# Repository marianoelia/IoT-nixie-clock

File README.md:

# Nixie Clock Project
[Link to hackster writeup tutorial](https://www.hackster.io/mrelia100/particle-photon-nixie-clock)

## Introduction
This is repo for my nixie clock build.

## License

This work is licensed under the  Creative Commons Attribution-ShareAlike 4.0 International License. To view a copy of this license, visit <http://creativecommons.org/licenses/by-sa/4.0/> or send a letter to Creative Commons, 444 Castro Street, Suite 900, Mountain View, California, 94041, USA.

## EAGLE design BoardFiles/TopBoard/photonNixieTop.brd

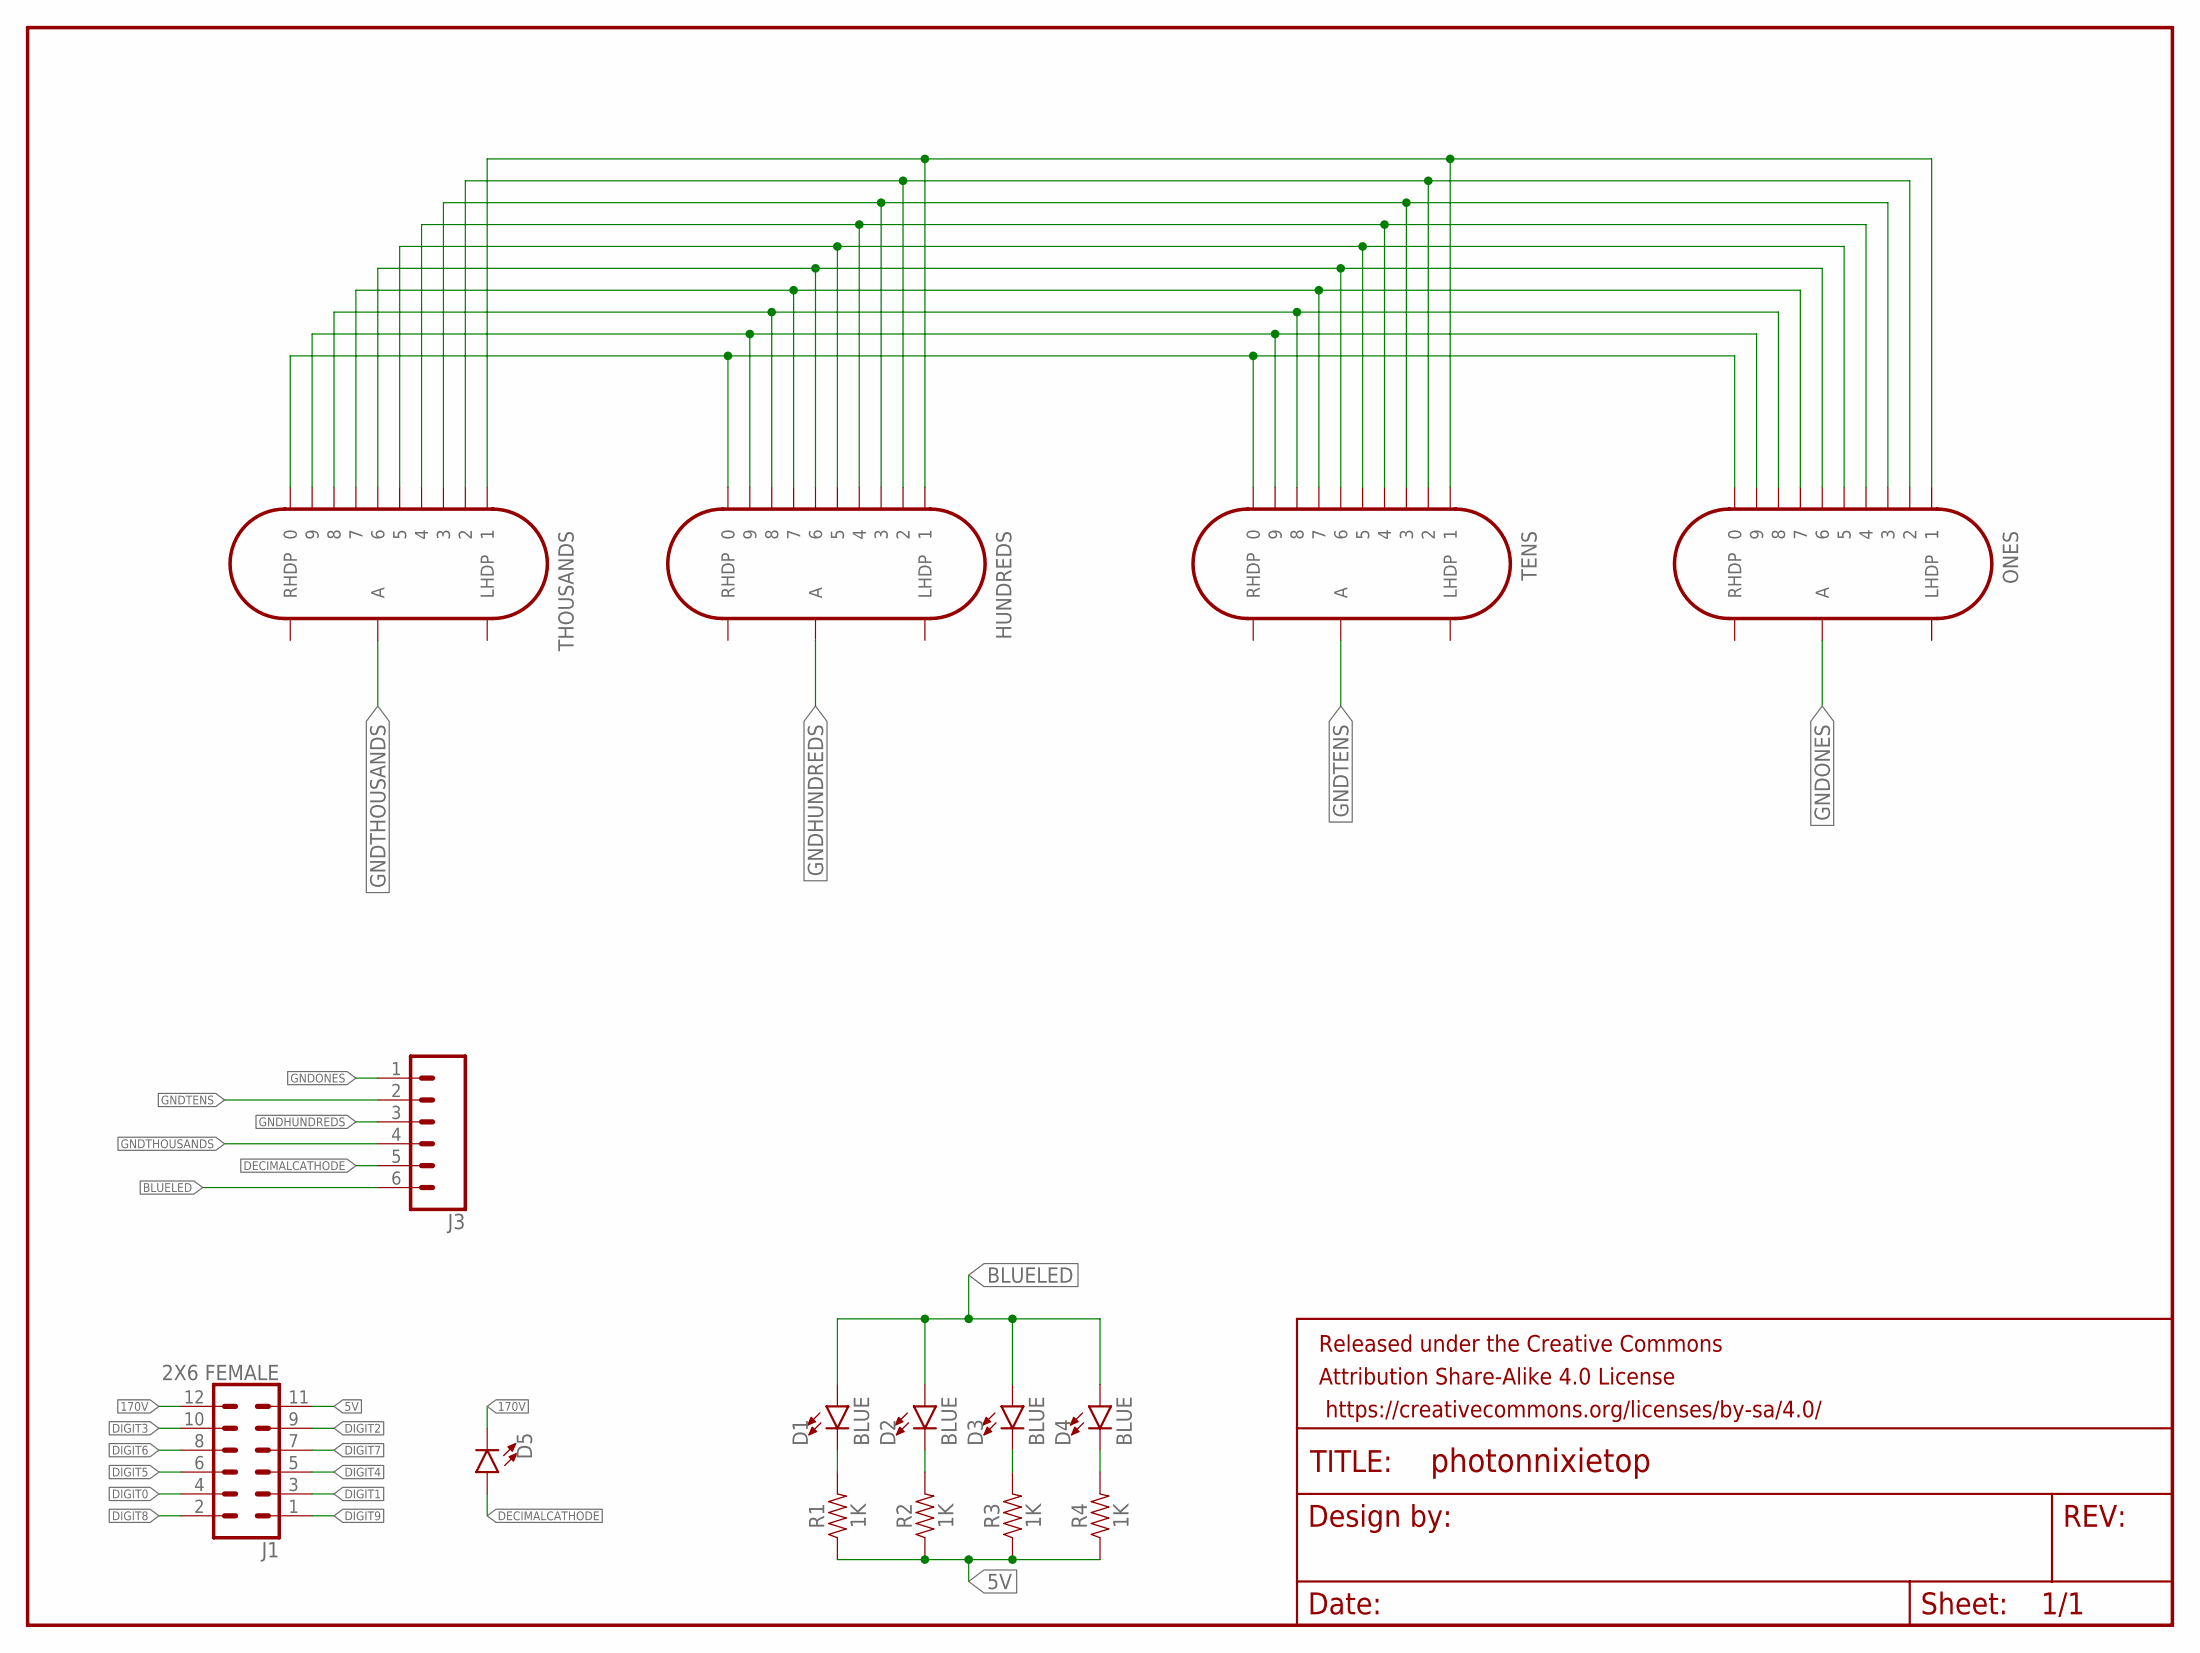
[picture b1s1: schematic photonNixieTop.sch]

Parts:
D1, D2, D3, D4: BLUE; LED-1206
D5: LED5MM; LED_5MM
FRAME1: FRAME-LETTER; CREATIVE_COMMONS
HUNDREDS: IN-14
J1: 2X6 FEMALE; 2X6
J3: CONN_06SILK_FEMALE_PTH; 1X06
ONES: IN-14
R1, R2, R3, R4: 1K; 0805
TENS: IN-14
THOUSANDS: IN-14

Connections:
5V: J1.11, R1.1, R2.1, R3.1, R4.1
170V: D5.K (C), J1.12
BLUELED: D1.A, D2.A, D3.A, D4.A, J3.6
DECIMALCATHODE: D5.A, J3.5
DIGIT0: HUNDREDS.0, J1.4, ONES.0, TENS.0, THOUSANDS.0
DIGIT1: HUNDREDS.1, J1.3, ONES.1, TENS.1, THOUSANDS.1
DIGIT2: HUNDREDS.2, J1.9, ONES.2, TENS.2, THOUSANDS.2
DIGIT3: HUNDREDS.3, J1.10, ONES.3, TENS.3, THOUSANDS.3
DIGIT4: HUNDREDS.4, J1.5, ONES.4, TENS.4, THOUSANDS.4
DIGIT5: HUNDREDS.5, J1.6, ONES.5, TENS.5, THOUSANDS.5
DIGIT6: HUNDREDS.6, J1.8, ONES.6, TENS.6, THOUSANDS.6
DIGIT7: HUNDREDS.7, J1.7, ONES.7, TENS.7, THOUSANDS.7
DIGIT8: HUNDREDS.8, J1.2, ONES.8, TENS.8, THOUSANDS.8
DIGIT9: HUNDREDS.9, J1.1, ONES.9, TENS.9, THOUSANDS.9
GNDHUNDREDS: HUNDREDS.A, J3.3
GNDONES: J3.1, ONES.A
GNDTENS: J3.2, TENS.A
GNDTHOUSANDS: J3.4, THOUSANDS.A
unnamed: D4.C, R4.2
unnamed: D3.C, R3.2
unnamed: D2.C, R2.2
unnamed: D1.C, R1.2

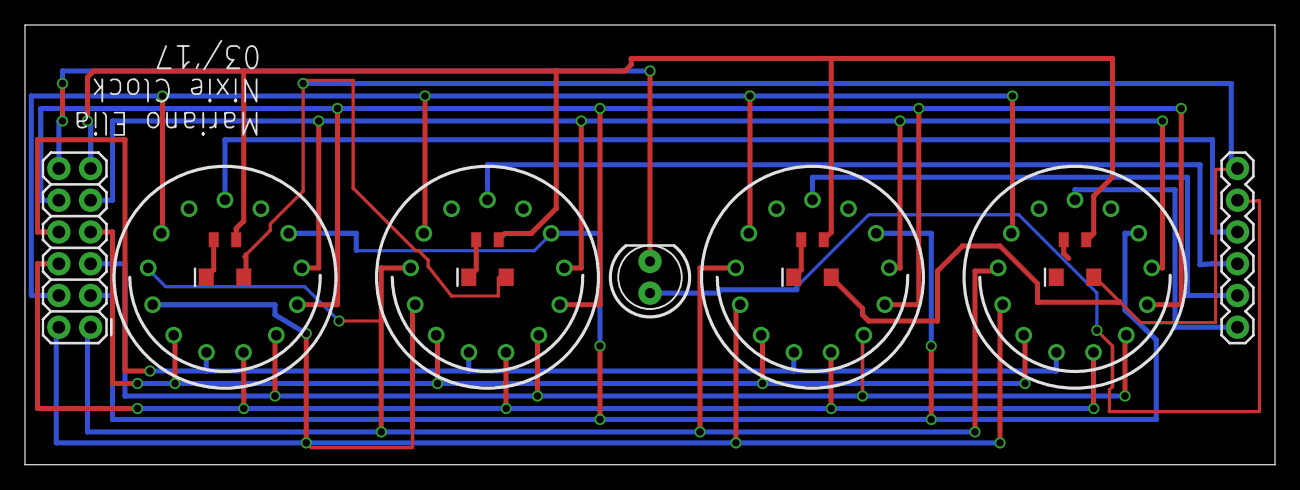
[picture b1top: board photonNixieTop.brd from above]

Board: 2 copper layers, 100.0 x 35.2 mm, 16 parts (0 on the bottom side), 22 nets.

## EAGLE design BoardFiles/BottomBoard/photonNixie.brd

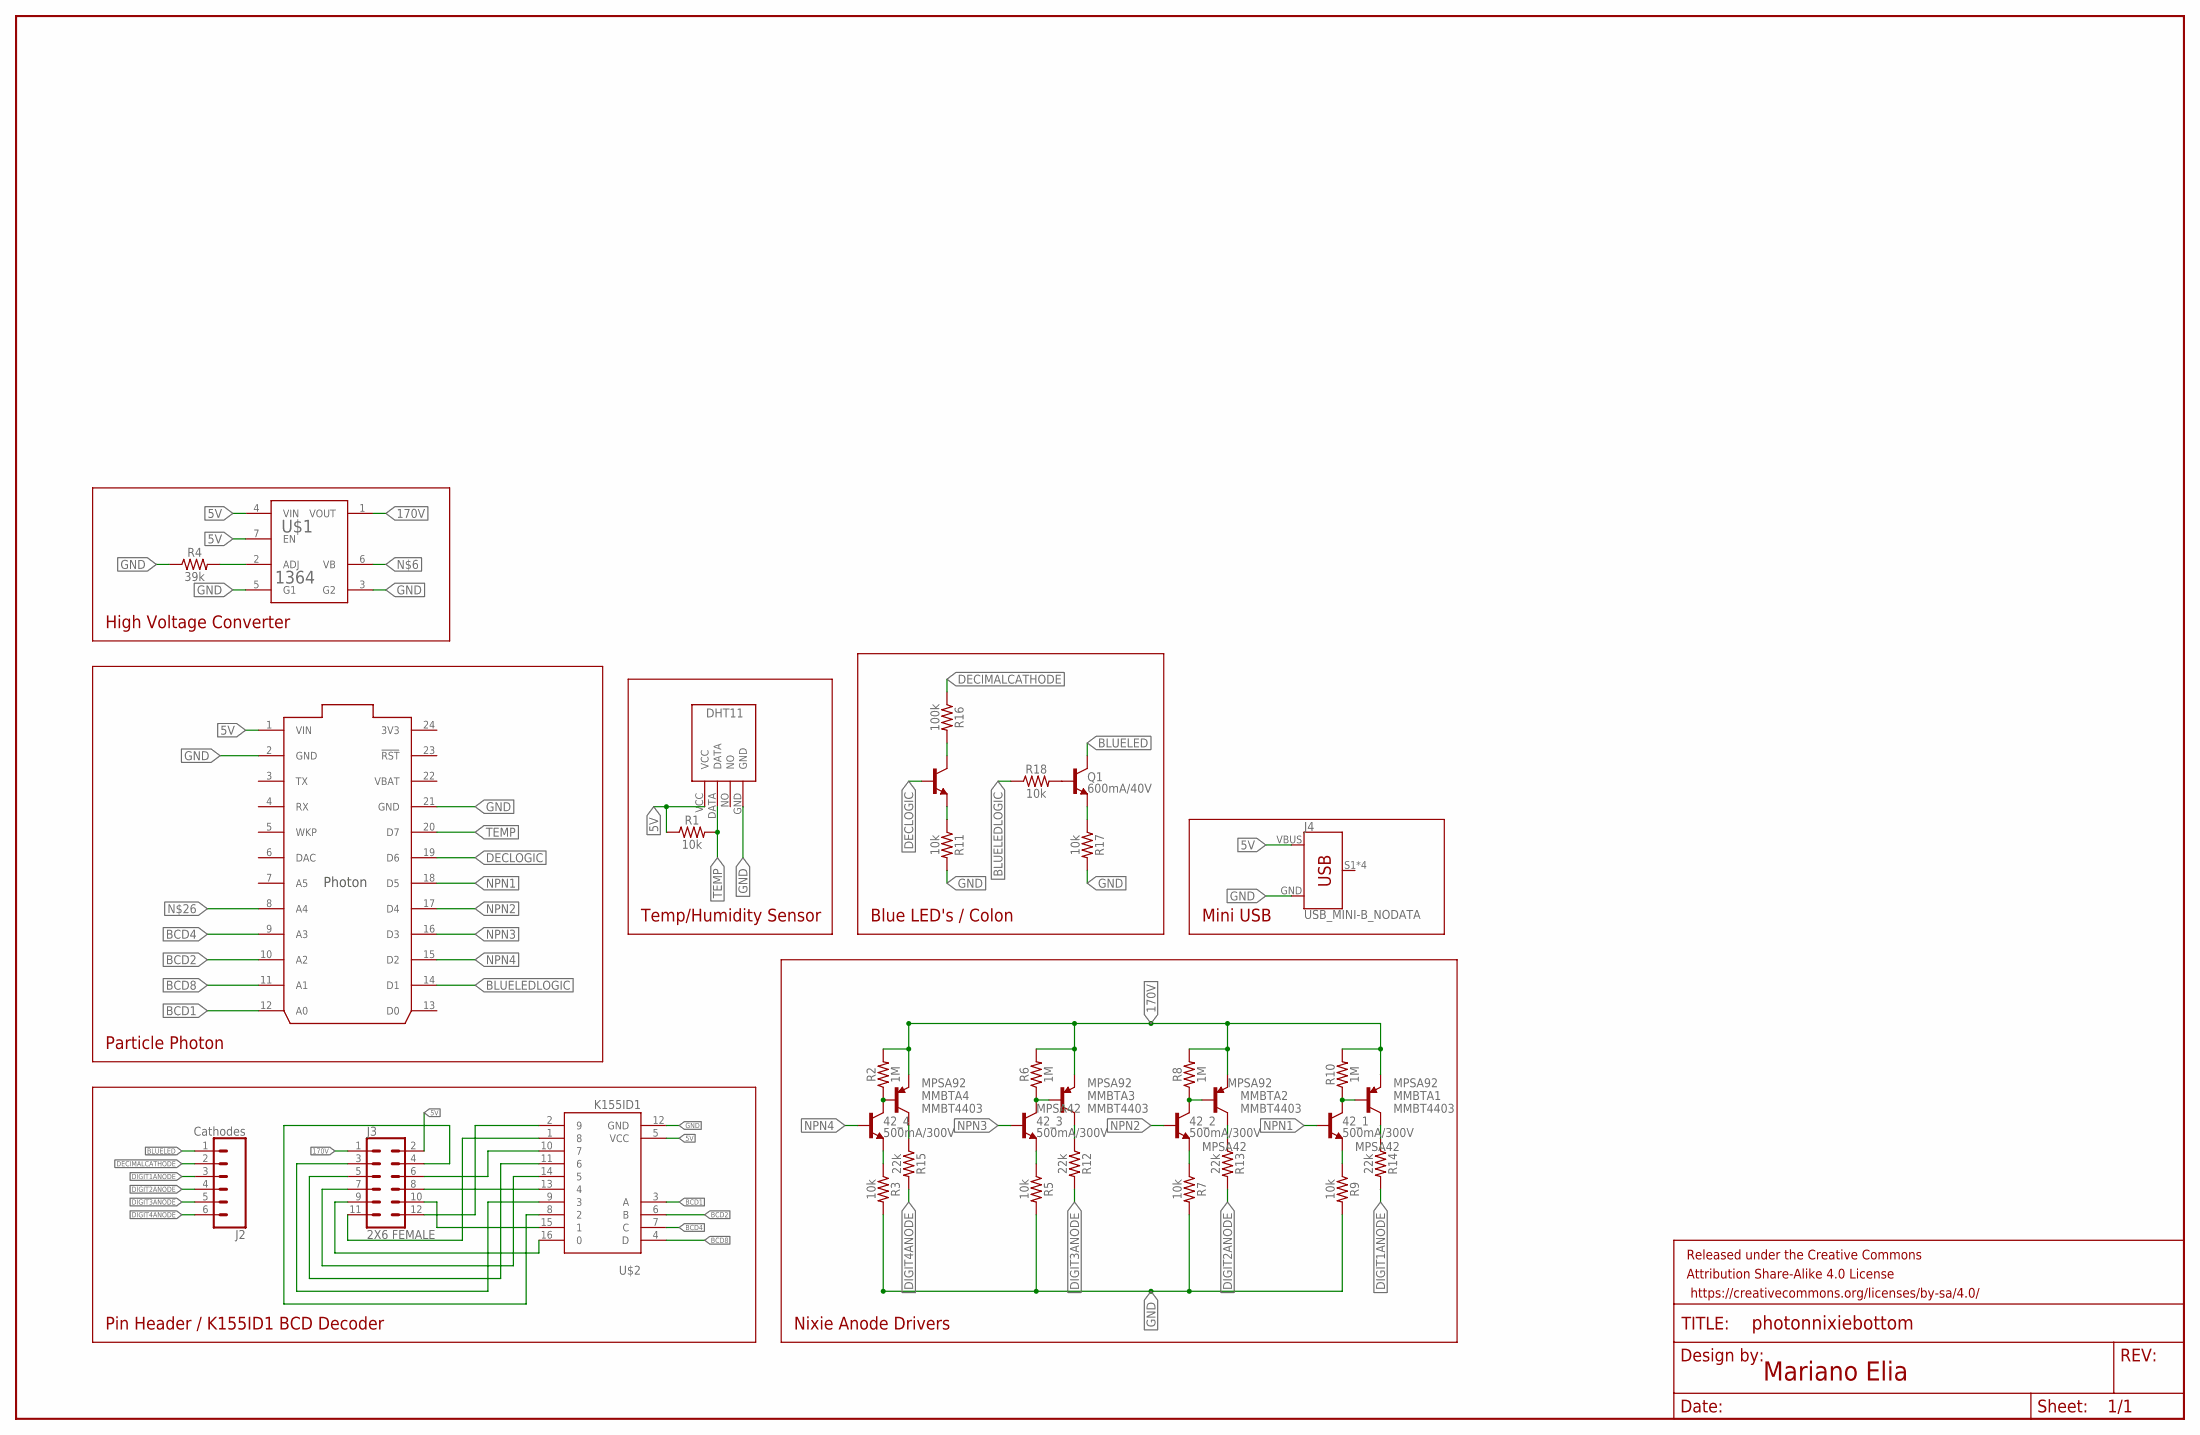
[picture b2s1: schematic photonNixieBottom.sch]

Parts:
42_1, 42_2, 42_3, 42_4: 500mA/300V; SOT23-3
FRAME1: FRAME-LEDGER; CREATIVE_COMMONS
J2: Cathodes; 1X06_NO_SILK
J3: 2X6 FEMALE; 2X6
J4: USB_MINI-B_NODATA; USB-MINIB_NODATA
MMBTA1, MMBTA2, MMBTA3, MMBTA4: MMBT4403; SOT23-3
MPSA7: 500mA/300V; SOT23-3
Q1: 600mA/40V; SOT23-3
R1, R3, R5, R7, R9, R11, R17, R18: 10k; 0805
R2, R6, R8, R10: 1M; 0805
R4: 39k; 0805
R12, R13, R14, R15: 22k; 0805
R16: 100k; 0805
U$1: 1364
U$2: K155ID1; DIL16-KIT
U$3: Temp/Humidity; DHT11
U$4: PHOTON_SMDNOSILK

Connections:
3V3: U$4.24 (3V3)
5V: J3.2, J4.VBUS, R1.1, U$1.4 (VIN), U$1.7 (EN), U$2.5 (VCC), U$3.VCC, U$4.1 (VIN)
170V: J3.1, MMBTA1.2 (E), MMBTA2.2 (E), MMBTA3.2 (E), MMBTA4.2 (E), R2.2, R6.2, R8.2, R10.2, U$1.1 (VOUT)
BCD1: U$2.3 (A), U$4.12 (A0)
BCD2: U$2.6 (B), U$4.10 (A2)
BCD4: U$2.7 (C), U$4.9 (A3)
BCD8: U$2.4 (D), U$4.11 (A1)
BLUELED: J2.1, Q1.3 (C)
BLUELEDLOGIC: R18.1, U$4.14 (D1)
DECIMALCATHODE: J2.2, R16.1
DECLOGIC: MPSA7.1 (B), U$4.19 (D6)
DIGIT1ANODE: J2.3, R14.2
DIGIT2ANODE: J2.4, R13.2
DIGIT3ANODE: J2.5, R12.2
DIGIT4ANODE: J2.6, R15.2
GND: J4.GND, R3.2, R4.1, R5.2, R7.2, R9.2, R11.2, R17.2, U$1.3 (G2), U$1.5 (G1), U$2.12 (GND), U$3.GND, U$4.2 (GND), U$4.21 (GND)
unnamed: J3.11, U$2.1 (8)
unnamed: J3.12, U$2.2 (9)
unnamed: R4.2, U$1.2 (ADJ)
unnamed: J3.9, U$2.16 (0)
unnamed: J3.10, U$2.15 (1)
unnamed: J3.7, U$2.14 (5)
unnamed: J3.8, U$2.13 (4)
unnamed: J3.5, U$2.11 (6)
unnamed: J3.6, U$2.10 (7)
unnamed: J3.3, U$2.9 (3)
unnamed: 42_4.2 (E), R3.1
unnamed: 42_3.2 (E), R5.1
unnamed: 42_4.3 (C), MMBTA4.1 (B), R2.1
unnamed: MPSA7.2 (E), R11.1
unnamed: 42_2.2 (E), R7.1
unnamed: 42_2.3 (C), MMBTA2.1 (B), R8.1
unnamed: J3.4, U$2.8 (2)
unnamed: 42_1.2 (E), R9.1
unnamed: 42_1.3 (C), MMBTA1.1 (B), R10.1
unnamed: 42_3.3 (C), MMBTA3.1 (B), R6.1
unnamed: MMBTA3.3 (C), R12.1
unnamed: MMBTA4.3 (C), R15.1
unnamed: MMBTA2.3 (C), R13.1
unnamed: MMBTA1.3 (C), R14.1
unnamed: MPSA7.3 (C), R16.2
unnamed: Q1.1 (B), R18.2
unnamed: Q1.2 (E), R17.1
NPN1: 42_1.1 (B), U$4.18 (D5)
NPN2: 42_2.1 (B), U$4.17 (D4)
NPN3: 42_3.1 (B), U$4.16 (D3)
NPN4: 42_4.1 (B), U$4.15 (D2)
TEMP: R1.2, U$3.DATA, U$4.20 (D7)
VBAT: U$4.22 (VBAT)

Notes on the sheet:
Particle Photon
Temp/Humidity Sensor
High Voltage Converter
Pin Header / K155ID1 BCD Decoder
Nixie Anode Drivers
Blue LED's / Colon
Mini USB
Mariano Elia

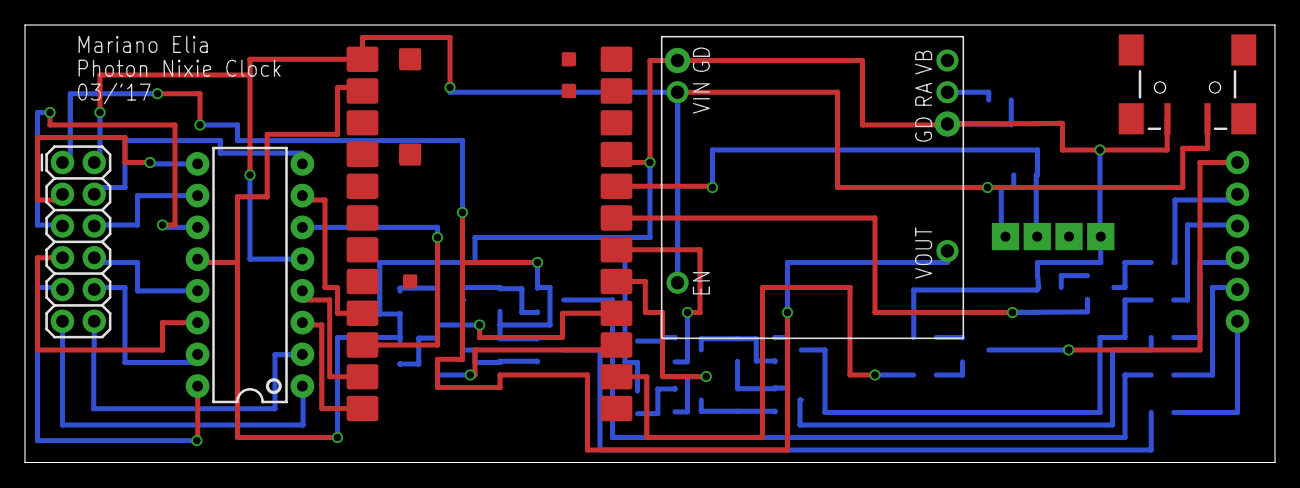
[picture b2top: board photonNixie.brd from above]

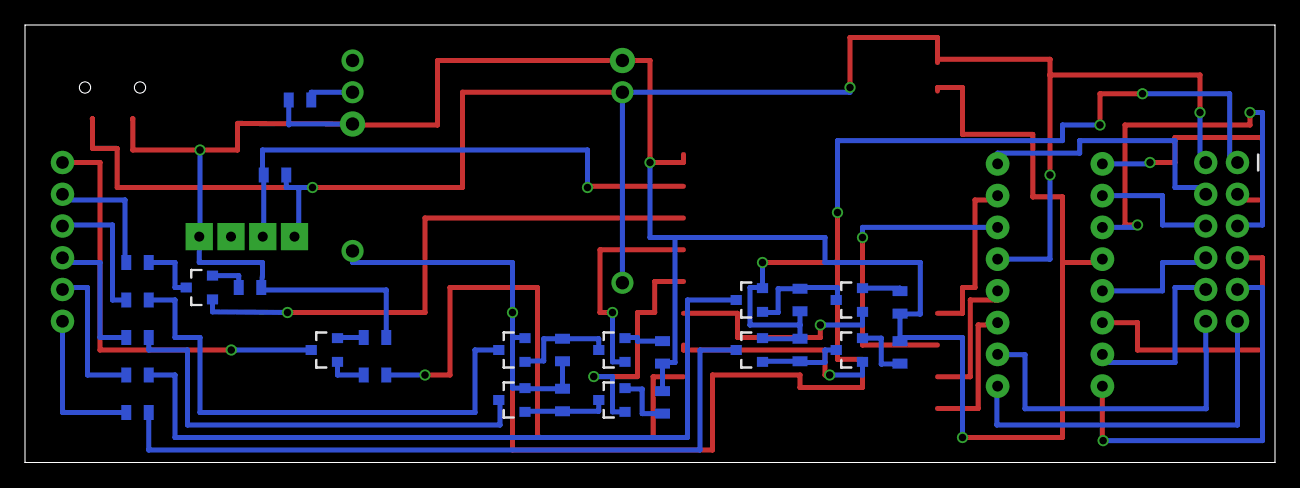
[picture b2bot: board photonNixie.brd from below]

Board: 2 copper layers, 100.0 x 35.0 mm, 36 parts (28 on the bottom side), 47 nets.

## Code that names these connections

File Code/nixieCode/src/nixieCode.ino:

/*
 * Project Particle Photon Nixie Clock
 * Description: Software to control 4 IN-14 Nixie tubes using my designed PCB's.
 * Link to repository: https://github.com/mrelia100/nixie-clock
 * Author: Mariano Elia
 * Date Published: June 5, 2018
 */

#include <Adafruit_DHT.h>

#define DHTPIN 7
#define DHTTYPE DHT11

int temperature, humidity;

DHT dht(DHTPIN, DHTTYPE);
//EEPROM Addresses
 int zoneAddress = 0;
 int lastLEDSetting = 1;

//Variable with
 int multiplexDelay = 1000;

//External Pins
 int digit1 = 5;
 int digit2 = 4;
 int digit3 = 3;
 int digit4 = 2;
 int colonPin = 6;
 int blueLEDPin = 1;

 int zone;
 int ledOnOff;
 long previousMillis = 0;

 int count = 0;
 int oldTime;
 const int segmentPins[4]={
     A1, A3, A2, A0
 };

 byte numbers[10][4] = {
  {0,0,0,1}, // 0
  {0,0,0,0}, // 1
  {1,0,0,1}, // 2
  {1,0,0,0}, // 3
  {0,1,1,1}, // 4
  {0,1,1,0}, // 5
  {0,1,0,1}, // 6
  {0,1,0,0}, // 7
  {0,0,1,1}, // 8
  {0,0,1,0}  // 9
  };

 void setup() {
    //Cloud particle funtions
     Particle.function("SetOffset", setZone);
     Particle.function("Scramble",scramble);
     Particle.function("Date", showDate);
     Particle.function("TurnLEDOn", blueLEDSwitch);
     Particle.function("Start Effect", startEffect);
     Particle.function("Get Temp", readTemperature);
     Particle.function("Get Humidity", readHumidity);
 pinMode(A0, OUTPUT);
 pinMode(A1, OUTPUT);
 pinMode(A2, OUTPUT);
 pinMode(A3, OUTPUT);

 pinMode(blueLEDPin, OUTPUT); //Pin to turn blue leds on/off
 pinMode(DHTPIN, INPUT); //Pin input from DHT11

 pinMode(digit1, OUTPUT);
 pinMode(digit2, OUTPUT);
 pinMode(digit3, OUTPUT);
 pinMode(digit4, OUTPUT);
 pinMode(colonPin, OUTPUT);

 getTimeZone();
 getLEDSettings();
 startEffect("1");
 oldTime = getTime();
 digitalWrite(colonPin, LOW);
 } ////////////// End of void setup()


 void loop(){
   unsigned long currentMillis = millis();
   showTime();
 if (currentMillis - previousMillis  > 60000){ //every 2 minutes
     previousMillis = currentMillis;
     scramble("1");
     showDate("1");
     scramble("1");
 }
 } ////////////// End of void loop()

 //used in showing digits but not called directly.
 void writeBCD(int n){
   for (int i = 0; i<4; i++){
     digitalWrite(segmentPins[i], numbers[n][i]);
   }
 }

 //Function showdigits takes a 4 digit number and displays it on the nixie tubes for a specific length of time.
 void showdigits(int number, int delayLength){ //number will be up to 4 long
 /* To show the multiplexing effect, anodes of the Nixie Tubes will be cycled
 */
 delayLength = delayLength/4;
 for (int current = 0; current<delayLength; current++){
  int thousands = number/1000;
  digitalWrite(digit4,LOW);
  writeBCD(thousands);
  if ( thousands == 20){ //0
     digitalWrite(digit1, LOW);
 }
 else{
   digitalWrite(digit1, HIGH);
   }
   digitalWrite(digit2, LOW);
   digitalWrite(digit3, LOW);
   delayMicroseconds(multiplexDelay);

 int hundreds = number%1000/100;
   digitalWrite(digit1, LOW);
   writeBCD(hundreds); //234/100 is 2.
   digitalWrite(digit2, HIGH);
   digitalWrite(digit3, LOW);
   digitalWrite(digit4, LOW);
   delayMicroseconds(multiplexDelay);

 int tens = ((number%1000)%100)/10;
   digitalWrite(digit1, LOW);
   digitalWrite(digit2, LOW);
   writeBCD(tens);
   digitalWrite(digit3, HIGH);
   digitalWrite(digit4, LOW);
   delayMicroseconds(multiplexDelay);

 int ones = ((number%1000)%100)%10;
   digitalWrite(digit1, LOW);
   digitalWrite(digit2, LOW);
   digitalWrite(digit3, LOW);
   writeBCD(ones);
   digitalWrite(digit4, HIGH);
   delayMicroseconds(multiplexDelay);
   digitalWrite(digit4, LOW);
 }
 }

 int scramble(String command){
 for (int i = 0; i<2; i++){
 for (int j = 0; j<=9999; j+=1111){
 showdigits(j, 30); //8
 }
 }
 return 1;
 }


 int showTime(){
 int hourPlusMinute = getTime();
 showdigits(hourPlusMinute,8);
 return hourPlusMinute;
 }


 int showDate(String command){
 int date = Time.month()*100+Time.day();
 showdigits(date, 3000);
     return 1;
 }


 //////////////////////////////////////////////// Time Functions ///////////////////////////

 void getTimeZone(){
     EEPROM.get(zoneAddress, zone);
     Time.zone(zone);
 }

 int blueLEDSwitch(String command){
     if (command == "1"){
      ledOnOff = 1;
     digitalWrite(blueLEDPin, ledOnOff);
     digitalWrite(colonPin, HIGH); //neon bulb
     EEPROM.put(lastLEDSetting, ledOnOff);
     return 1;
     }
     else {
         ledOnOff = 0;
     digitalWrite(blueLEDPin, ledOnOff);
     digitalWrite(colonPin, LOW); //neon bulb
     EEPROM.put(lastLEDSetting, ledOnOff);
     return 1;
     }
     return 0;
 }

 void getLEDSettings(){
     EEPROM.get(lastLEDSetting, ledOnOff);
     if (ledOnOff == 1) {
     digitalWrite(blueLEDPin, HIGH);
   }
     else {
     digitalWrite(blueLEDPin, LOW);
 }
 }


 int getTime(){
    Time.zone(zone);
     int hourPlusMinute = (Time.hourFormat12())*100+Time.minute();
 return hourPlusMinute;
 }

 int setZone(String command){
     zone = command.toInt();
     EEPROM.put(zoneAddress, zone);
 return 1;
 }

 /*
 * Start effect starts at 00:00 and cycles the minutes digit a couple times before
 * landing on the correct digit. It then proceeds to the tens digit and cycles it.
 */
 int startEffect(String command){
    int fullTime = getTime(); //Receive function in full form, eg 1230
    int ones = ((fullTime%1000)%100)%10;
    int tens = ((fullTime%1000)%100)/10;
    int hundreds = fullTime%1000/100;
     showdigits(0000,1000);

     for (int i = 0; i<4; i++){
         if (i ==0){
     for (int j = 0; j<9; j++){
         String string = "000";
         String numToString = String(j);
         string.concat(numToString);
         int number = string.toInt();
         showdigits(number, 30);
     }
         }

     if (i == 1){
         for (int j = 0; j<9; j++){
         String string = "00";
         String numToString = String(j);
         string.concat(numToString);
         string.concat(ones);
         int number = string.toInt();
         showdigits(number, 30);
     }
     }

         if (i == 2){
         for (int j = 0; j<9; j++){
         String string = "0";
         String numToString = String(j);
         string.concat(numToString);
         string.concat(tens);
         string.concat(ones);
         int number = string.toInt();
         showdigits(number, 30);
     }
     }
         if (i == 3){
         for (int j = 0; j<9; j++){
         String string = "";
         String numToString = String(j);
         string.concat(numToString);
         string.concat(hundreds);
         string.concat(tens);
         string.concat(ones);
         int final = string.toInt();
         showdigits(final, 30);
     }
     }

  }
    showdigits(fullTime, 4000);
   return 1;
 }

int readTemperature(String command){
temperature = dht.getTempCelcius();
delay(10);
return temperature;
 }

 int readHumidity(String command){
humidity = dht.getHumidity();
delay(10);
return humidity;
 }

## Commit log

2018-06-03 added picture
2018-06-03 removed photo
2018-06-03 Added solidworks files
2018-06-03 Added photos
2018-06-03 Added stl of base
2018-06-03 Added code init
2018-06-03 Added libraries
2018-06-04 Added Datasheets
2018-06-04 Added eagle boards
2018-06-04 Added top board
2018-06-04 added more pics
2018-06-05 Changed 3D case and updated code
2018-06-06 library addition
2018-06-07 Code and case changes

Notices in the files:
parts and their libraries:
SparkFun-Connectors: Licensing: Creative Commons ShareAlike 4.0 International - https://creativecommons.org/licenses/by-sa/4.0
SparkFun-Aesthetics: Released under the Creative Commons Attribution Share-Alike 4.0 License
SparkFun-Aesthetics: https://creativecommons.org/licenses/by-sa/4.0
